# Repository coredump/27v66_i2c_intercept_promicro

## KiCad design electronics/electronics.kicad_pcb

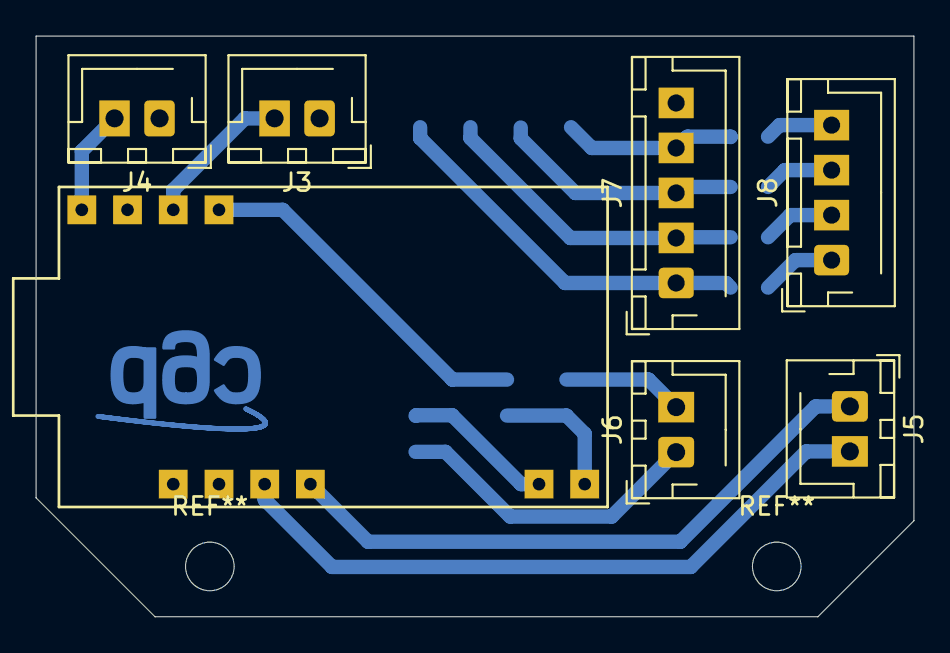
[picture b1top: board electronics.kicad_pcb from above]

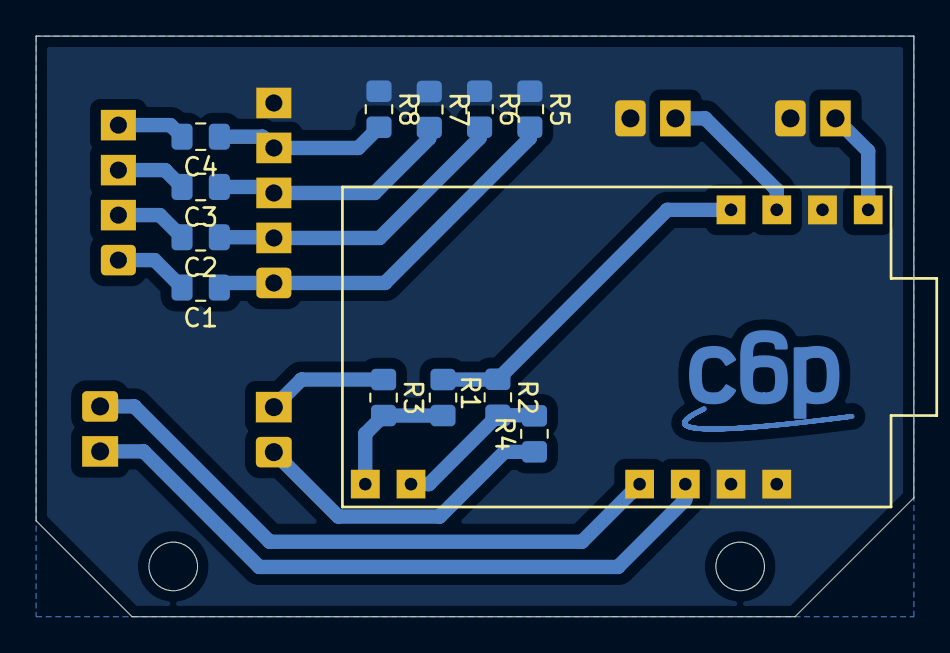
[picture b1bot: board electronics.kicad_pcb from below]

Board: 2 copper layers, 48.8 x 32.3 mm, 20 parts (12 on the bottom side), 18 nets.

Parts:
C1, C2, C3, C4: 0u1; C_0805_2012Metric_Pad1.18x1.45mm_HandSolder
J3: EXTERNAL CONTROL; JST_XH_B2B-XH-AM_1x02_P2.50mm_Vertical
J4: POWER; JST_XH_B2B-XH-AM_1x02_P2.50mm_Vertical
J5, J6: I2C BUS; JST_XH_B2B-XH-AM_1x02_P2.50mm_Vertical
J7: INPUT; JST_XH_B5B-XH-AM_1x05_P2.50mm_Vertical
J8: OUTPUT; JST_XH_B4B-XH-AM_1x04_P2.50mm_Vertical
R1, R2: 4k7; R_0805_2012Metric_Pad1.20x1.40mm_HandSolder
R3, R4: 100; R_0805_2012Metric_Pad1.20x1.40mm_HandSolder
R5, R6, R7, R8: 75; R_0805_2012Metric_Pad1.20x1.40mm_HandSolder
U1: ProMicro
c6p_logo: G***; c6p-dev

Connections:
BIN: C3.1, J7.3, R7.2
BOUT: C3.2, J8.3
GIN: C2.1, J7.2, R6.2
GND: J3.1, J4.1, J7.5, R5.1, R6.1, R7.1, R8.1, U1.3, U1.4, U1.23
GOUT: C2.2, J8.2
unnamed: J6.1, R4.1
unnamed: J6.2, R3.1
RAW: J4.2, U1.24
RESET: J3.2, U1.22
RIN: C1.1, J7.1, R5.2
ROUT: C1.2, J8.1
SCL1: J5.1, U1.6
SCL2: R2.2, R4.2, U1.11
SDA1: J5.2, U1.5
SDA2: R1.2, R3.2, U1.12
SYNCIN: C4.1, J7.4, R8.2
SYNCOUT: C4.2, J8.4
VCC: R1.1, R2.1, U1.21

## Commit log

2021-07-27 Tested
2021-07-30 Let's try somethiing else
2021-08-05 Let's try something else
2021-08-07 Let's try without ic2
2021-08-07 This is bullshit
2021-08-10 Working version with Pro Micro
2021-08-10 Adds kicad project
2021-08-10 Adds LICENSE
2021-08-10 Adding PDF schematics
2021-08-10 Changed some art
2021-08-26 Last through hole
2021-09-01 Encoder support
2021-09-01 Remove failed pcb attempts
2021-09-01 Updated schematics/pdf
2021-09-01 Fix encoder name on the schematic
